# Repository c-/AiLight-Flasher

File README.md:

# Overview

This is a simple programming/flashing PCB for an AiLight ESP-8266 "smart
bulb". It's not the first and probably not the best, but I'm happy with it.

There are some designs that use pogo pins in 3D-printed "frames".
[I tried one; didn't like](Pictures/IMG_20190811_100513.jpg).
Alignment is difficult, and it really needs both hands to
position and hold. Precision in 3D printing isn't really high enough to get
the pins to line up exactly.

But in the spirit of "when all you have is a hammer", I have a PCB mill...

# Design

The alignment problem is addressed using a couple of pins which fit into
a pair of holes in the the AiLight board. It turns out that 14 gauge
copper electrical wire with a slightly rounded tip fits these holes
precisely enough that the pogo pins will easily hit their target pads.

Otherwise, it's just a simple breakout board for the standard 6-pin FTDI
header, with a jumper to control whether it's in flash mode (disabling
flash is useful to see if the programming worked).
 
# Manufacturing

I milled it on my 1610 CNC using a 0.5mm V-bit with 1.0mm drill plus a 1.2mm
bit for the larger holes and outline. Your workflow may vary. The front
"silk screen" was done with a marker held
[in a pen holder](https://www.thingiverse.com/thing:2851655).

You could likely send the project to a board manufacturer, but be aware
that I may not have handled the internal cutout properly. Clearances are
designed for coarse PCB milling, so it should fall well within the design rules
of any manufacturer.

# Parts

1. PCB
2. (5) pogo pins, 1mm OD
3. two pieces of 14 gauge copper wire (1.7mm dia) approx 10cm long,
tips slightly rounded
4. 1x06 socket strip (right angle pins might be better, haven't tried)
5. 1x02 pin header and jumper

The wire pins should be long enough to insert and handle while soldering.
Rounding the tips can be done by holding them in a drill chuck and running
it against a file.

# Assembly

Start with the alignment pins. I went with approx 5mm projection on the
back side of the board. Solder.

Solder the pogo pins next. I found them to be a tight fit. The tips should
project just slightly further (maybe 0.5mm) than the alignment pins. You
might want to check the fit against an actual board since the necessary
projection depends on how pointy you make the alignment pins.

Solder the rest of the components.

# Using

I can hold it single-handed. Connect the FTDI board, align the
pins, press down slightly on the pogo pin side, connect the USB, and flash
from whatever IDE you're using. Remove the jumper if you need to check the
results (you may need to disconnect/reconnect the FTDI cable).

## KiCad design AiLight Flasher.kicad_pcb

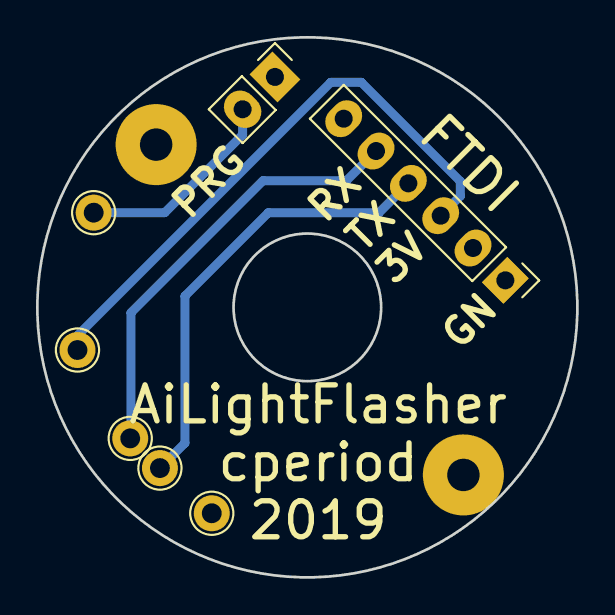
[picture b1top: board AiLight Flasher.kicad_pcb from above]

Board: 2 copper layers, 30.0 x 30.0 mm, 9 parts (0 on the bottom side), 5 nets.

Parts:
H1: Align1; SolderWirePad_single_2mmDrill
H2: Align2; SolderWirePad_single_2mmDrill
J1: GND; Test_Point_THTPad_d2.0mm_Drill1.1mm
J2: IO0; Test_Point_THTPad_d2.0mm_Drill1.1mm
J3: 3V3; Test_Point_THTPad_d2.0mm_Drill1.1mm
J4: aRX; Test_Point_THTPad_d2.0mm_Drill1.1mm
J5: aTX; Test_Point_THTPad_d2.0mm_Drill1.1mm
J6: FTDI; Socket_Strip_Straight_1x06_Oval_Pitch2.54mm
JP1: Jumper; Socket_Strip_Straight_1x02_Oval_Pitch2.54mm

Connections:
3V3: J3.1, J6.3
GND: J1.1, J6.1, JP1.1
unnamed: J2.1, JP1.2
aRX: J4.1, J6.4
aTX: J5.1, J6.5

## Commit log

2019-06-02 initial git import
2019-06-02 add a jumper to IO0 so we can use the serial monitor to check if it flashed
2019-06-03 bump the size slightly, flip the FTDI header around to give more space
2019-06-03 move the aux origin to account for the size bump
2019-06-06 more position tweaks
2019-06-06 move the FTDI header back out a bit, tweak labels, etc
2019-08-11 didn't entirely like how that one trace hit the pad.
2019-08-11 write the fine manual
2019-08-11 wrong photo
